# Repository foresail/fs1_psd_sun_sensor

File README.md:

# Foresail-1 PSS Sun Sensor

This repository contains the public available design files for the PSS sun sensor designed for the Foresail-1 Cubesat.

The performance and testing of this sensor has been documented in [this article](https://doi.org/10.1016/j.asr.2026.01.083).

The general characteristics of sensor design are:
- Dimensions: 24 mm × 16 mm × 6 mm
- Mass: 4 grams
- Panel mountedable into 14x14 mm hole with two M2 screws.
- Electrical connection by soldering on the panel PCB or by harness.
- FOV: ~100 degrees, resolution: 0.13°, accuracy: ±1°
- Refresh rate up to 100 Hz. (Sampling time: 4 ms + communication overhead)
- Can provide following data products:
    - Raw current measurements
    - Point & intensity measurements
    - Sun vector & intensity measurements
    - Angles & intensity measurements
- I2C digital serial interface (hardware version 3)
- RS-485 digital interface (hardware version 4)
- Low power consumption < 4 mW when active
- Nominal operating voltage: 3.6 - 3.8V: Can be extened easily to 2.0 – 5.5 V.

## Documentation

- [Research Paper](https://doi.org/10.1016/j.asr.2026.01.083)
- [FS1 ADCS PSS Sun Sensor Design Document](docs/FS1p_ADCS_PSS_Sun_Sensor_Design_Document.pdf)
- [Version 3 schematic (I2C variant)](v3/pss_v3_schema.pdf)
- [Version 3 firmware source code](v3/fw)
- [Version 4 schematic (RS-485 variant)](v4/pss_v4_schema.pdf)
- [Version 4 firmware source code](v4/fw)
- [Calibration and test tools for PC](calibration)
- [Mechanical design files](mechanical)

## Licence

The design is licenced under [CERN Open Hardware Licence Version 2](LICENCE)

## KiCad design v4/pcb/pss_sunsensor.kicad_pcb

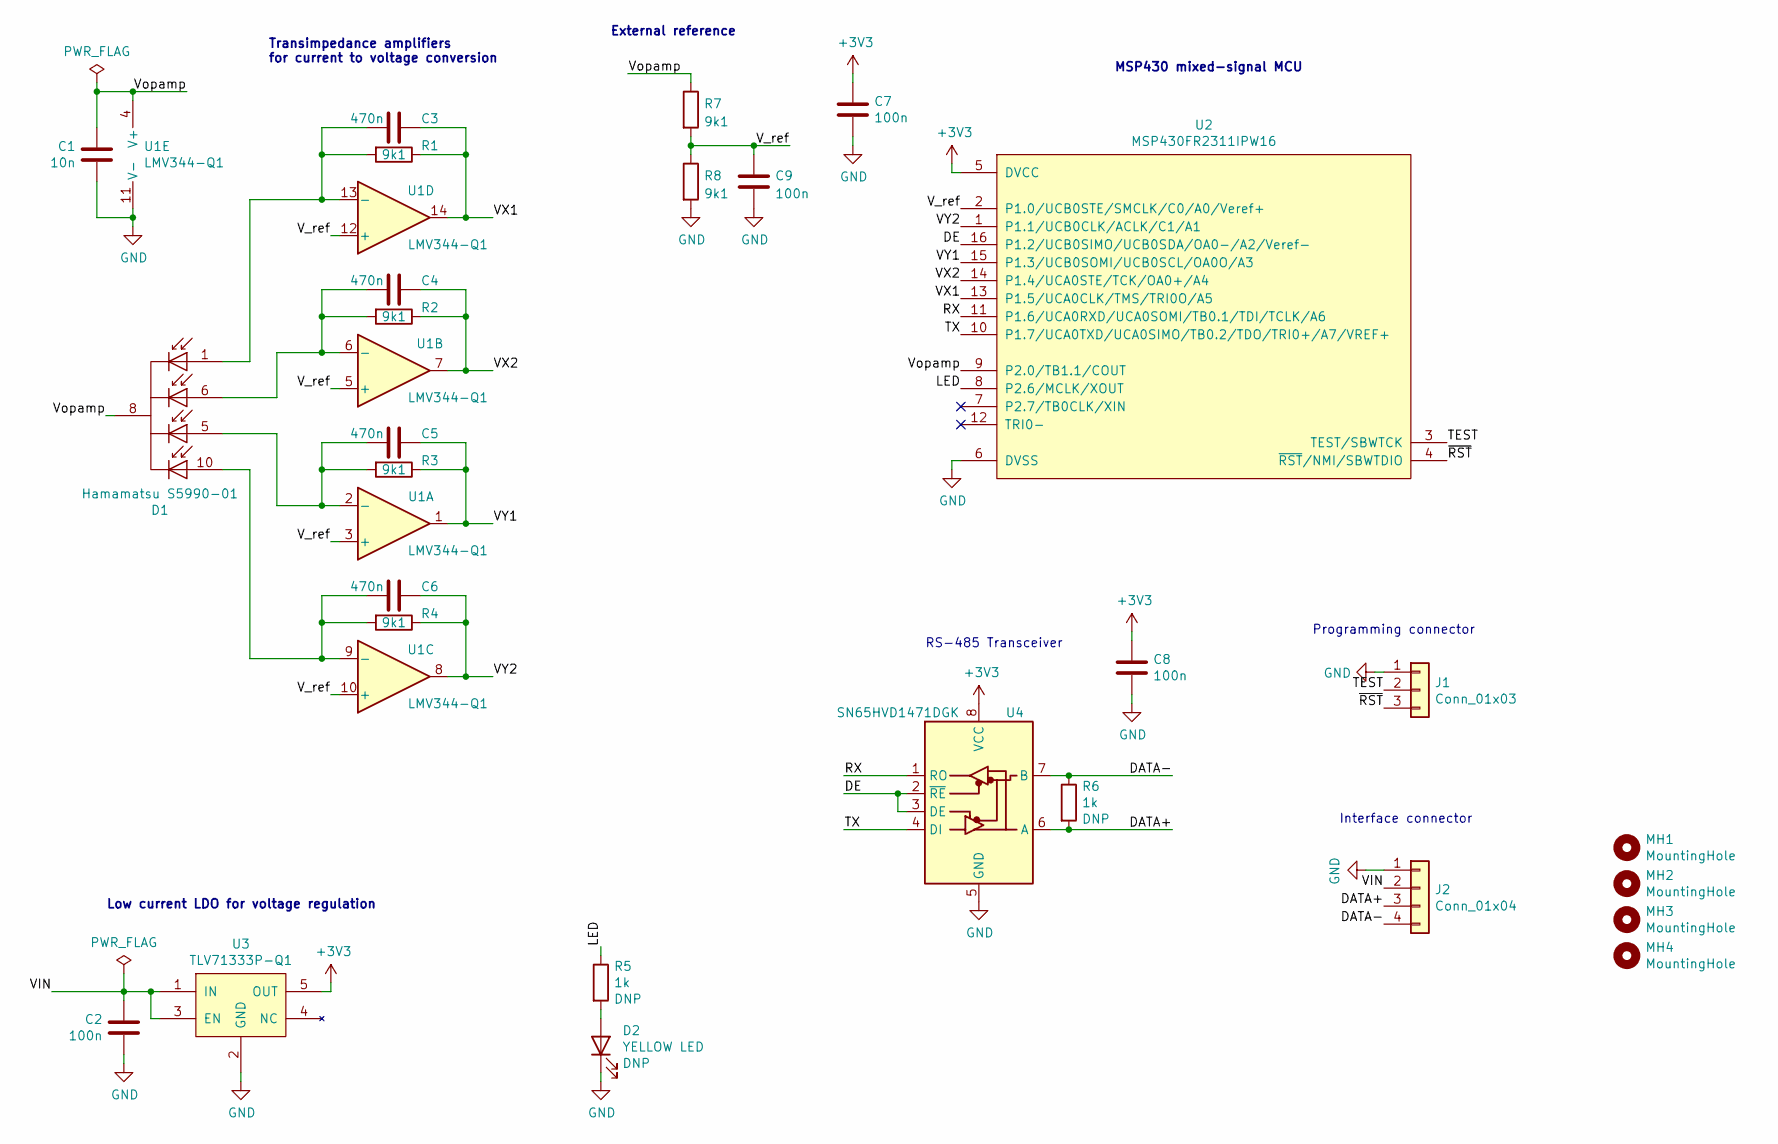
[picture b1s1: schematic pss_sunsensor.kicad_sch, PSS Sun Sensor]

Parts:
C1: 10n; C_0402_1005Metric
C2, C7, C8, C9: 100n; C_0402_1005Metric
C3, C4, C5, C6: 470n; C_0402_1005Metric
D1: Hamamatsu S5990-01; Hamatsu_S5980
D2: YELLOW LED; LED_0402_1005Metric
J1: Conn_01x03; PinHeader_1x03_P1.27mm_Vertical
J2: Conn_01x04; PinHeader_1x04_P1.27mm_Horizontal
MH1, MH2, MH3, MH4: MountingHole; MountingHole_2.2mm_M2
R1, R2, R3, R4, R7, R8: 9k1; R_0402_1005Metric
R5: 1k; R_0402_1005Metric
R6: 1k; R_0603_1608Metric
U1: LMV344-Q1; TSSOP-14_4.4x5mm_P0.65mm; Mouser 595-LMV344IPWRQ1
U2: MSP430FR2311IPW16; TSSOP-16_4.4x5mm_P0.65mm; Mouser 595-P430FR2311IPW16R
U3: TLV71333P-Q1; SOT-23-5; Mouser 595-TLV71333PQDBVRQ1
U4: SN65HVD1471DGK; VSSOP-8_2.4x2.1mm_P0.5mm

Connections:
+3V3: C7.2, C8.2, U2.5 (DVCC), U3.5 (OUT), U4.8 (VCC)
/DATA+: J2.3, R6.2, U4.6 (A)
/DATA-: J2.4, R6.1, U4.7 (B)
/DE: U2.16 (P1.2/UCB0SIMO/UCB0SDA/OA0-/A2/Veref-), U4.2 (~RE), U4.3 (DE)
/LED: R5.1, U2.8 (P2.6/MCLK/XOUT)
/RX: U2.11 (P1.6/UCA0RXD/UCA0SOMI/TB0.1/TDI/TCLK/A6), U4.1 (RO)
/TEST: J1.2, U2.3 (TEST/SBWTCK)
/TX: U2.10 (P1.7/UCA0TXD/UCA0SIMO/TB0.2/TDO/TRI0+/A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), U4.4 (DI)
/VIN: C2.2, J2.2, U3.1 (IN), U3.3 (EN)
/VX1: C3.1, R1.1, U1.14, U2.13 (P1.5/UCA0CLK/TMS/TRI0O/A5)
/VX2: C4.1, R2.1, U1.7, U2.14 (P1.4/UCA0STE/TCK/OA0+/A4)
/VY1: C5.1, R3.1, U1.1, U2.15 (P1.3/UCB0SOMI/UCB0SCL/OA0O/A3)
/VY2: C6.1, R4.1, U1.8, U2.1 (P1.1/UCB0CLK/ACLK/C1/A1)
/V_ref: C9.2, R7.2, R8.1, U1.3 (+), U1.5 (+), U1.10 (+), U1.12 (+), U2.2 (P1.0/UCB0STE/SMCLK/C0/A0/Veref+)
/Vopamp: C1.2, D1.8 (Cathode), R7.1, U1.4 (V+), U2.9 (P2.0/TB1.1/COUT)
/~RST: J1.3, U2.4 (~RST/NMI/SBWTDIO)
GND: C1.1, C2.1, C7.1, C8.1, C9.1, D2.1 (K), J1.1, J2.1, R8.2, U1.11 (V-), U2.6 (DVSS), U3.2 (GND), U4.5 (GND)
unnamed: C3.2, D1.1 (Anode_X1), R1.2, U1.13 (-)
unnamed: C4.2, D1.6 (Anode_X2), R2.2, U1.6 (-)
unnamed: C5.2, D1.5 (Anode_Y1), R3.2, U1.2 (-)
unnamed: C6.2, D1.10 (Anode_Y2), R4.2, U1.9 (-)
unnamed: D2.2 (A), R5.2

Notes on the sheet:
RS-485 Transceiver
Transimpedance amplifiers for current to voltage conversion
External reference
Low current LDO for voltage regulation
Programming connector
MSP430 mixed-signal MCU
Interface connector

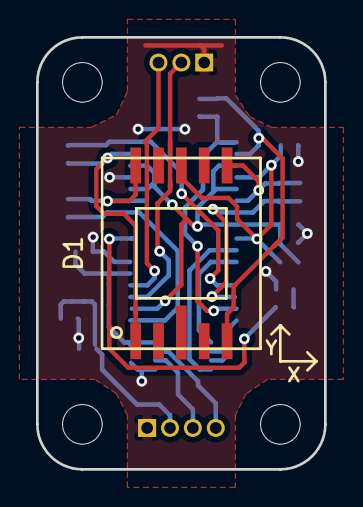
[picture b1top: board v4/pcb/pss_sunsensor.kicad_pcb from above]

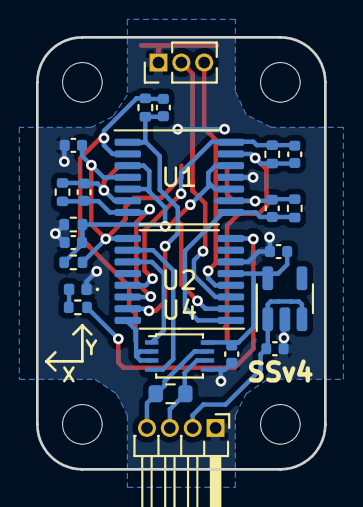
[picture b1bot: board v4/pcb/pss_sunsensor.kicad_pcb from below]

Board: 2 copper layers, 16.0 x 24.0 mm, 29 parts (24 on the bottom side), 22 nets.

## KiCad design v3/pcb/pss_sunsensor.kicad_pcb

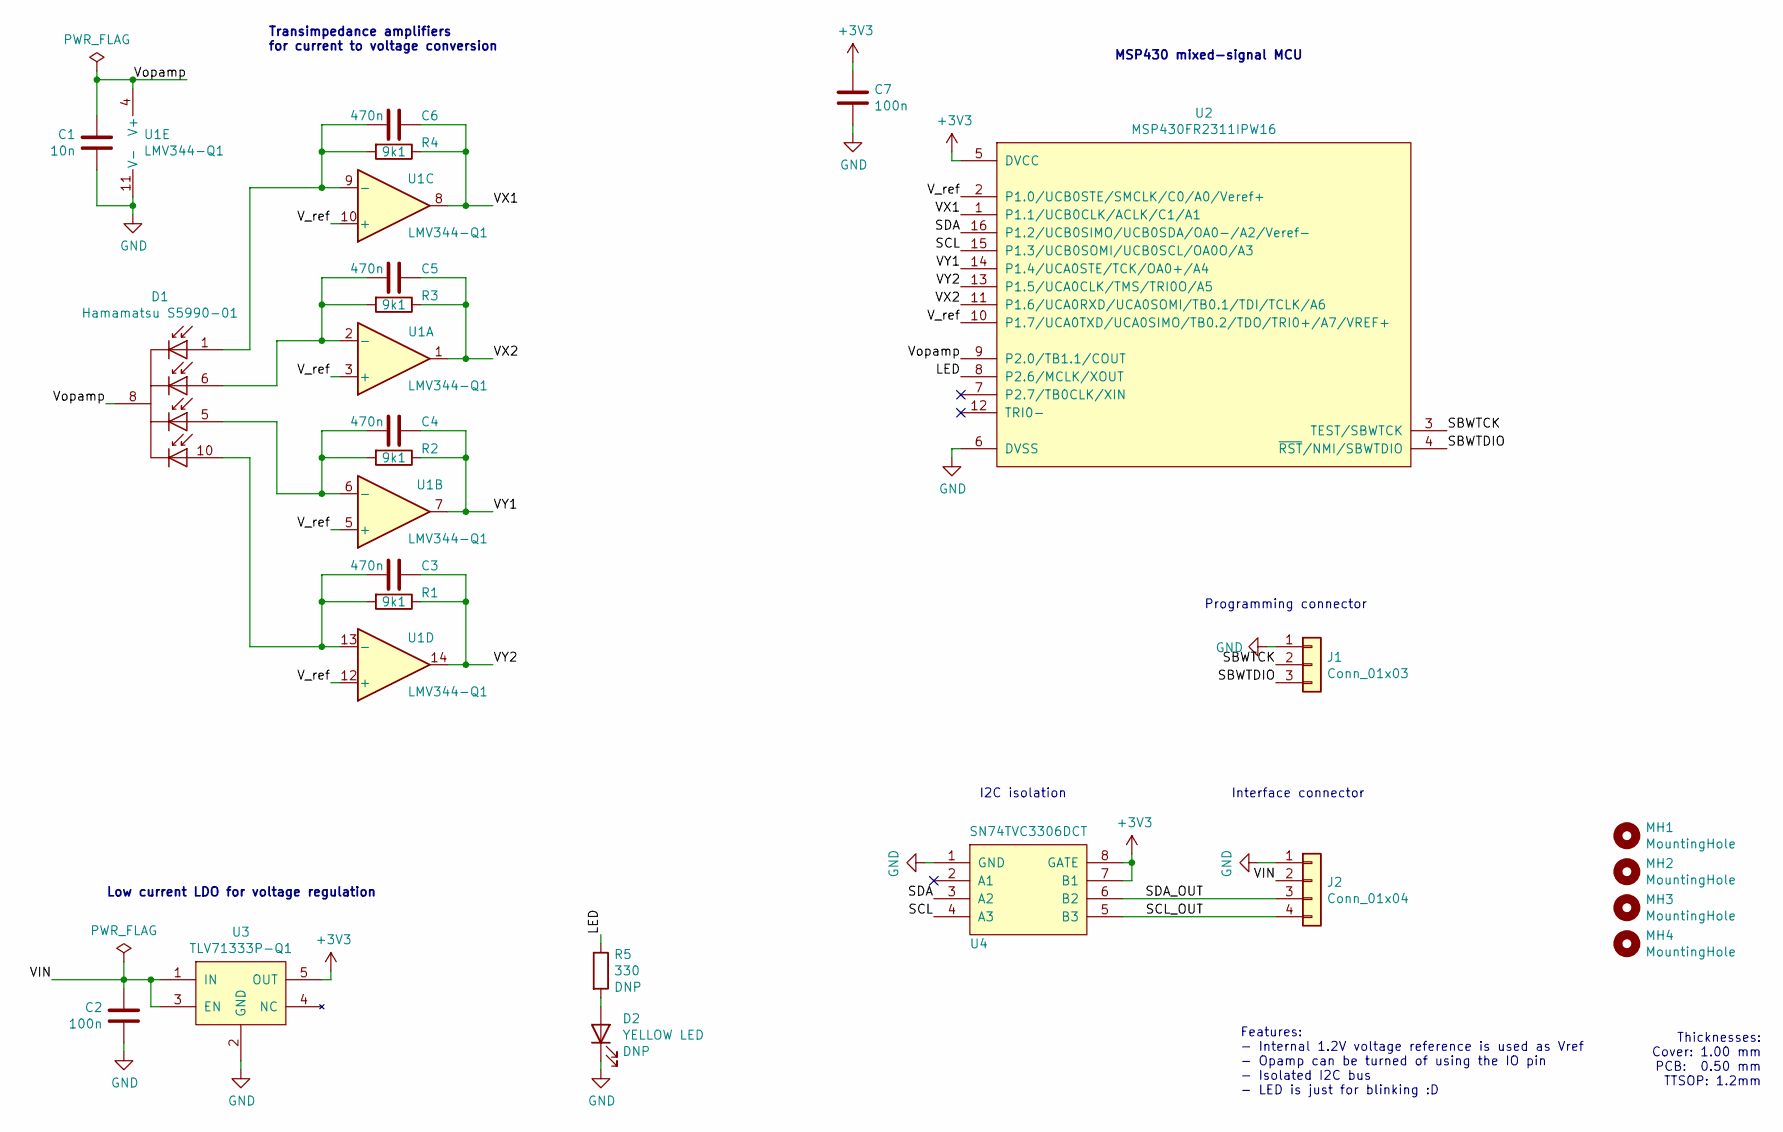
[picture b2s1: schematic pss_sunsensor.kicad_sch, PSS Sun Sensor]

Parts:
C1: 10n; C_0603_1608Metric
C2, C7: 100n; C_0603_1608Metric
C3, C4, C5, C6: 470n; C_0603_1608Metric
D1: Hamamatsu S5990-01; Hamatsu_S5980
D2: YELLOW LED; LED_0603_1608Metric
J1: Conn_01x03; PinHeader_1x03_P1.27mm_Vertical
J2: Conn_01x04; PinHeader_1x04_P1.27mm_Horizontal
MH1, MH2, MH3, MH4: MountingHole; MountingHole_2.2mm_M2
R1, R2, R3, R4: 9k1; R_0603_1608Metric
R5: 330; R_0603_1608Metric
U1: LMV344-Q1; TSSOP-14_4.4x5mm_P0.65mm; Mouser 595-LMV344IPWRQ1
U2: MSP430FR2311IPW16; TSSOP-16_4.4x5mm_P0.65mm; Mouser 595-P430FR2311IPW16R
U3: TLV71333P-Q1; SOT-23-5; Mouser 595-TLV71333PQDBVRQ1
U4: SN74TVC3306DCT; VSSOP-8_2.4x2.1mm_P0.5mm

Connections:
+3V3: C7.2, U2.5 (DVCC), U3.5 (OUT), U4.7 (B1), U4.8 (GATE)
/LED: R5.1, U2.8 (P2.6/MCLK/XOUT)
/SBWTCK: J1.2, U2.3 (TEST/SBWTCK)
/SBWTDIO: J1.3, U2.4 (~RST/NMI/SBWTDIO)
/SCL: U2.15 (P1.3/UCB0SOMI/UCB0SCL/OA0O/A3), U4.4 (A3)
/SCL_OUT: J2.4, U4.5 (B3)
/SDA: U2.16 (P1.2/UCB0SIMO/UCB0SDA/OA0-/A2/Veref-), U4.3 (A2)
/SDA_OUT: J2.3, U4.6 (B2)
/VIN: C2.2, J2.2, U3.1 (IN), U3.3 (EN)
/VX1: C6.1, R4.1, U1.8, U2.1 (P1.1/UCB0CLK/ACLK/C1/A1)
/VX2: C5.1, R3.1, U1.1, U2.11 (P1.6/UCA0RXD/UCA0SOMI/TB0.1/TDI/TCLK/A6)
/VY1: C4.1, R2.1, U1.7, U2.14 (P1.4/UCA0STE/TCK/OA0+/A4)
/VY2: C3.1, R1.1, U1.14, U2.13 (P1.5/UCA0CLK/TMS/TRI0O/A5)
/V_ref: U1.3 (+), U1.5 (+), U1.10 (+), U1.12 (+), U2.2 (P1.0/UCB0STE/SMCLK/C0/A0/Veref+), U2.10 (P1.7/UCA0TXD/UCA0SIMO/TB0.2/TDO/TRI0+/A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)
/Vopamp: C1.2, D1.8 (Cathode), U1.4 (V+), U2.9 (P2.0/TB1.1/COUT)
GND: C1.1, C2.1, C7.1, D2.1 (K), J1.1, J2.1, U1.11 (V-), U2.6 (DVSS), U3.2 (GND), U4.1 (GND)
unnamed: C6.2, D1.1 (Anode_X1), R4.2, U1.9 (-)
unnamed: C5.2, D1.6 (Anode_X2), R3.2, U1.2 (-)
unnamed: C4.2, D1.5 (Anode_Y1), R2.2, U1.6 (-)
unnamed: C3.2, D1.10 (Anode_Y2), R1.2, U1.13 (-)
unnamed: D2.2 (A), R5.2

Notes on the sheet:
Programming connector
Features: - Internal 1.2V voltage reference is used as Vref - Opamp can be turned of using the IO pin - Isolated I2C bus - LED is just for blinking :D
MSP430 mixed-signal MCU
Thicknesses: Cover: 1.00 mm PCB: 0.50 mm TTSOP: 1.2mm
Transimpedance amplifiers for current to voltage conversion
Interface connector
Low current LDO for voltage regulation
I2C isolation

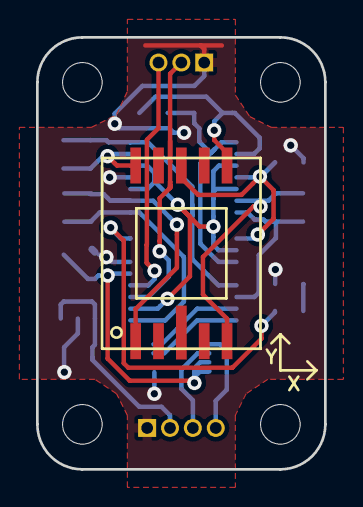
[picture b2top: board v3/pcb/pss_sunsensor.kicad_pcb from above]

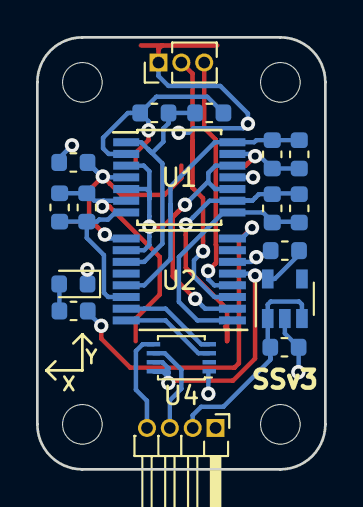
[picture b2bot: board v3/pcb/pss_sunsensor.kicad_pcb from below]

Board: 2 copper layers, 16.0 x 24.0 mm, 24 parts (19 on the bottom side), 21 nets.

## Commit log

2023-01-26 Add v3 and v4 design files
2026-03-24 Update README with performance article link
    Added a reference to the performance and testing article for the PSS sun sensor.
